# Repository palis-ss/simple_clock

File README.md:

# simple_clock

## Description
This repository contains the firmware for a replacement clock that I put into an old chassis.  The old clock was an analog clock.  I rebuilt a new one as a digital clock using 7-segment LEDs.  It uses the Blue Pill board ([Link](https://stm32-base.org/boards/STM32F103C8T6-Blue-Pill)) as its processor and relies on the RTC module of the STM32.  I removed the battery and replaced with a DC jack.  I also added a backup battery for the RTC.

The replacement clock must fit in the old chassis, so I made a bracket with 3D printing.  The mainboard that holds the Blue Pill and the 7-segments was designed in Eagle, which the schematics and gerber files are included in this repo.

For the firmware, the project was created using STM32CubeMX which uses STM32 HAL as the library.  The code is actually simple but I made it look harder than it actually is.  The big chunk of code is how I handle buttons.  The part about time keeping is not so much as the RTC on this MCU is very easy to use.  Nonetheless, there are a number of problems with the HAL library.  I'm listing the ones that affected this project here.
- The RTC's `HAL_RTC_GetTime` must be followed by the `HAL_RTC_GetDate` in order for it to work properly.
- The initialization routine `MX_RTC_Init`, by default, intializes the RTC's time to 0.  This part must be removed manually in order to use backup time from RTC.
- The default IRQ handler for Systick Interrupt is not called in the interrupt routine.  You must add it manually.  This part is a minor problem and not relevant to this project but I use it so I decided to mention here anyway.

## Notes on Board Assembling
- Make sure to take care of vias first if you develop the board yourself.
- Then do the MAX7219 next as it needs to be soldered on both sides.
- The rest of components can be soldered anytime afterwards.

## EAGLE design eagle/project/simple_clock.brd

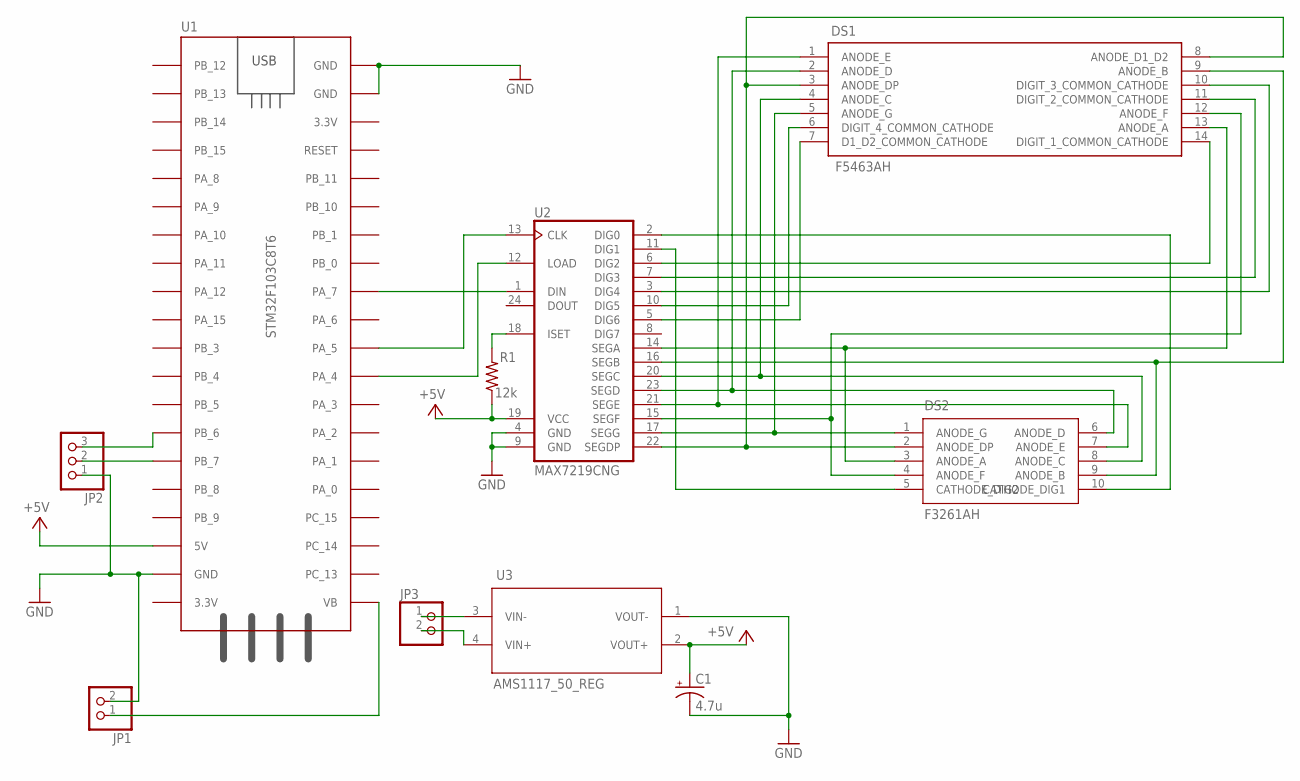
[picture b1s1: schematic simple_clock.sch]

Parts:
C1: 4.7u; E1,8-4
DS1: F5463AH
DS2: F3261AH
JP1, JP3: PINHD-1X2; 1X02
JP2: PINHD-1X3; 1X03
R1: 12k; 0207/12
U1: STM32F103C8T6
U2: MAX7219CNG; DIL24-3
U3: AMS1117_50_REG

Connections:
+5V: C1.+, R1.1, U1.5V, U2.19 (VCC), U3.2 (VOUT+)
GND: C1.-, JP1.2, JP2.1, U1.GND_1 (GND), U1.GND_2 (GND), U1.GND_3 (GND), U2.4 (GND), U2.9 (GND), U3.1 (VOUT-)
unnamed: DS1.10 (DIGIT_3_COMMON_CATHODE), U2.3 (DIG4)
unnamed: DS1.7 (D1_D2_COMMON_CATHODE), U2.5 (DIG6)
unnamed: U1.PA_7, U2.1 (DIN)
unnamed: DS1.14 (DIGIT_1_COMMON_CATHODE), U2.6 (DIG2)
unnamed: DS2.10 (CATHODE_DIG1), U2.2 (DIG0)
unnamed: DS2.5 (CATHODE_DIG2), U2.11 (DIG1)
unnamed: DS1.11 (DIGIT_2_COMMON_CATHODE), U2.7 (DIG3)
unnamed: DS1.6 (DIGIT_4_COMMON_CATHODE), U2.10 (DIG5)
unnamed: U1.PA_5, U2.13 (CLK)
unnamed: U1.PA_4, U2.12 (LOAD)
unnamed: DS1.13 (ANODE_A), DS2.3 (ANODE_A), U2.14 (SEGA)
unnamed: DS1.1 (ANODE_E), DS2.7 (ANODE_E), U2.21 (SEGE)
unnamed: DS1.12 (ANODE_F), DS2.4 (ANODE_F), U2.15 (SEGF)
unnamed: DS1.4 (ANODE_C), DS2.8 (ANODE_C), U2.20 (SEGC)
unnamed: DS1.2 (ANODE_D), DS2.6 (ANODE_D), U2.23 (SEGD)
unnamed: DS1.3 (ANODE_DP), DS1.8 (ANODE_D1_D2), DS2.2 (ANODE_DP), U2.22 (SEGDP)
unnamed: DS1.5 (ANODE_G), DS2.1 (ANODE_G), U2.17 (SEGG)
unnamed: R1.2, U2.18 (ISET)
unnamed: JP1.1, U1.VB
unnamed: JP2.2, U1.PB_7
unnamed: JP2.3, U1.PB_6
unnamed: JP3.1, U3.3 (VIN-)
unnamed: JP3.2, U3.4 (VIN+)
unnamed: DS1.9 (ANODE_B), DS2.9 (ANODE_B), U2.16 (SEGB)

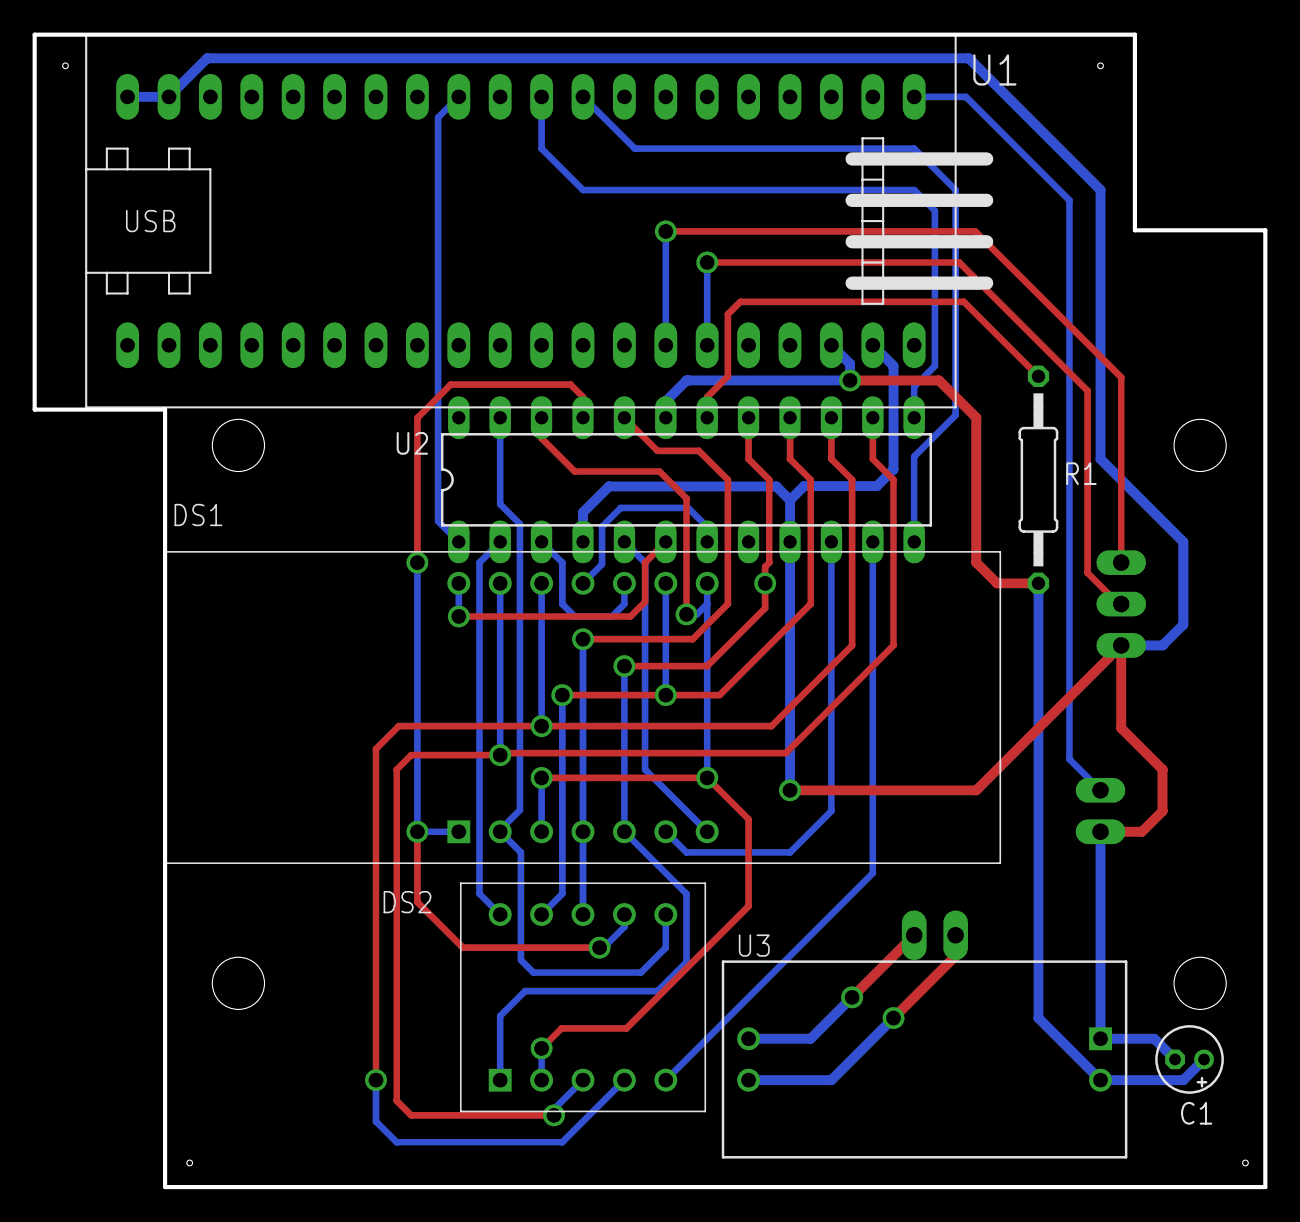
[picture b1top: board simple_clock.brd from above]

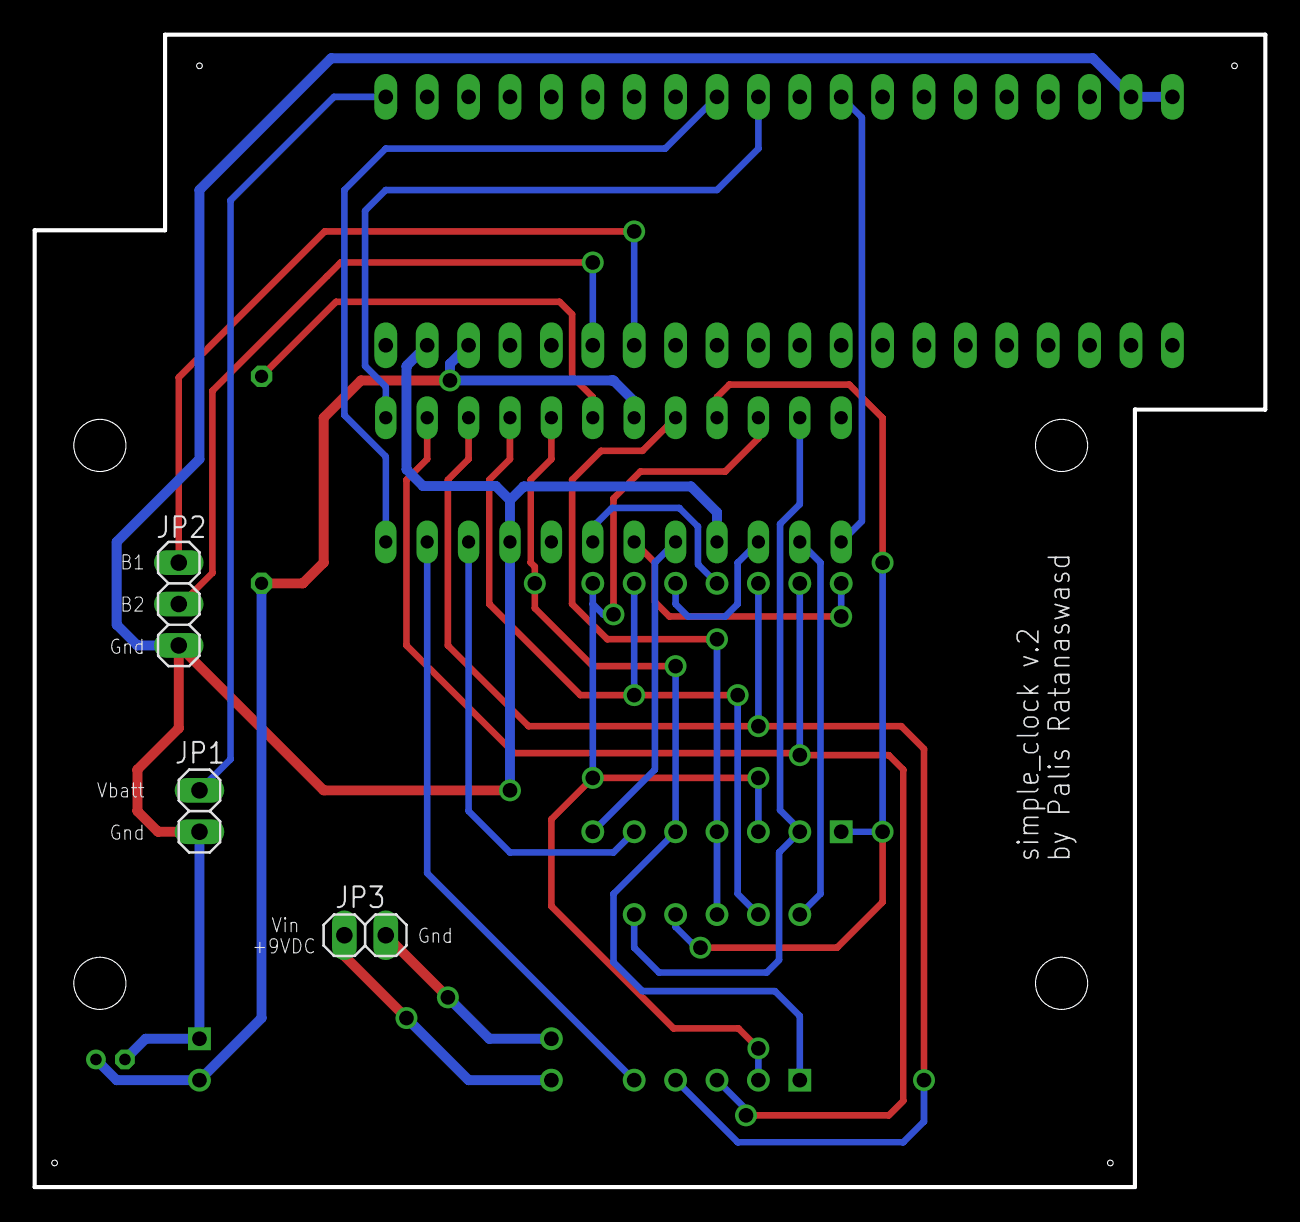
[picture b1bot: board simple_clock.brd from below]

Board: 2 copper layers, 75.5 x 70.7 mm, 10 parts (3 on the bottom side), 26 nets.

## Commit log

2019-12-02 update lib
2019-12-03 added eagle files
2019-12-03 added component
2019-12-10 made pcb in Eagle
2019-12-12 created Gerber files
2019-12-15 ready to make pcb
2019-12-20 updated board design
2019-12-22 updated footprints
2019-12-29 revised pcb
2020-01-01 updated firmware
2020-05-10 converted project into STM32CubeIDE
2020-05-10 Updated .gitignore
2020-05-10 Revert "Updated .gitignore"
    This reverts commit 256bb35cb6e6fce5e971f1c2e53c1165c5c89be3.
